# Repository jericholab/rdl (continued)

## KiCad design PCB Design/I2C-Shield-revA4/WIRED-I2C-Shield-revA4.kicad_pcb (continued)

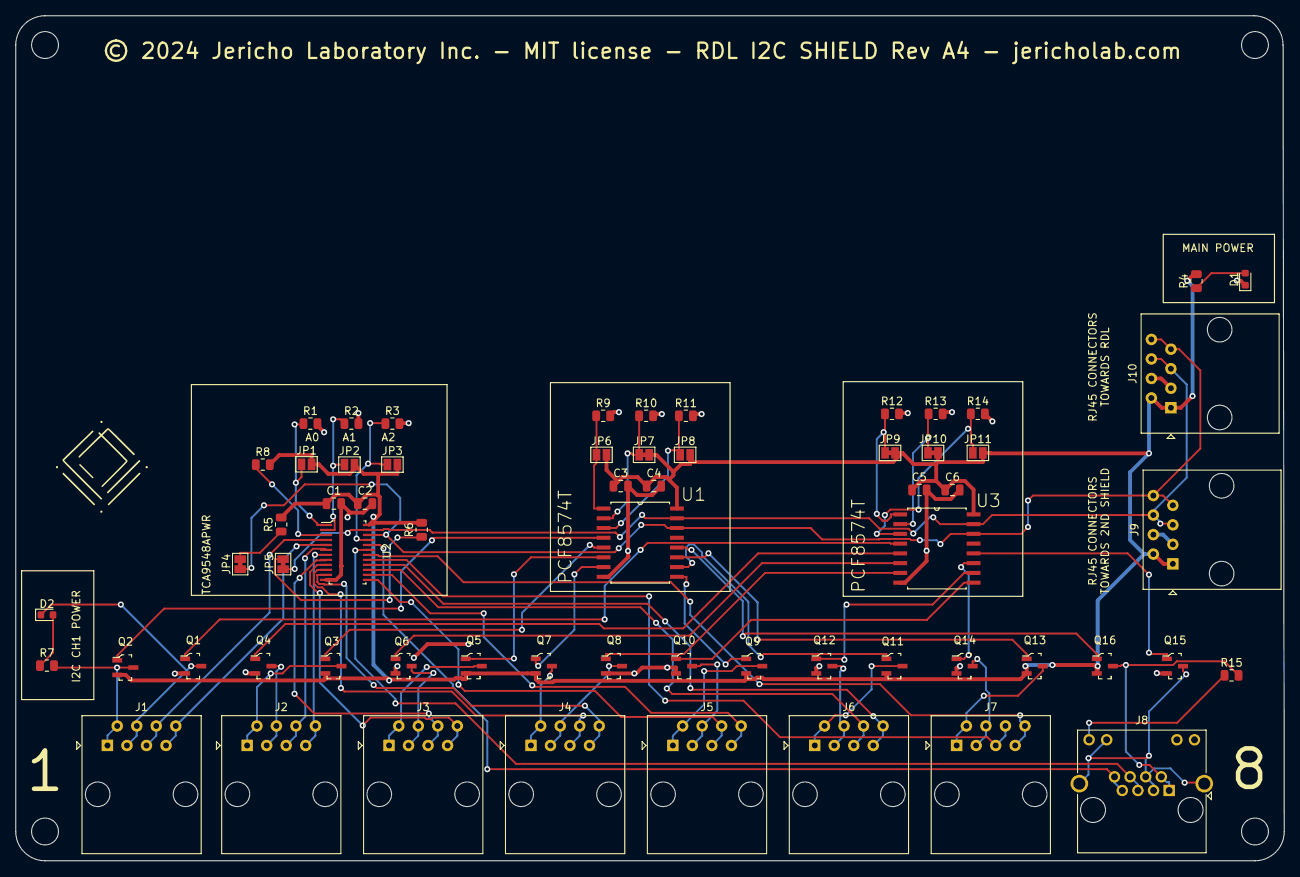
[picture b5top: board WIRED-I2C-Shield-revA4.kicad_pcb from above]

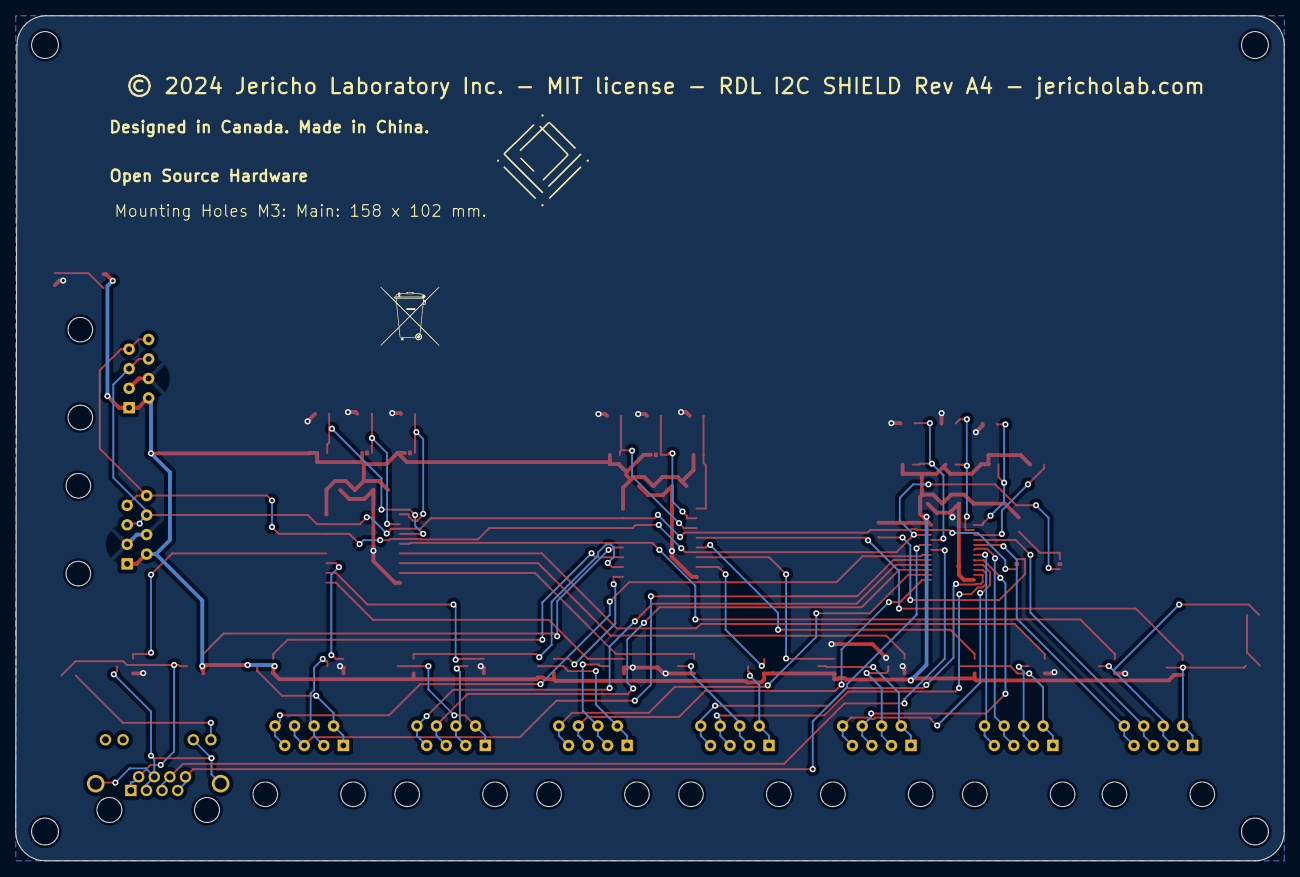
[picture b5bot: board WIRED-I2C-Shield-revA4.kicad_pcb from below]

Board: 2 copper layers, 165.1 x 110.0 mm, 70 parts (2 on the bottom side), 67 nets.

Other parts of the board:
G1, G2: LOGO; jericho-logo-kicad
G3: LOGO; Do not throw to garbage logo WEEE2
H1, H2, H3, H4: MountingHole_3.5mm

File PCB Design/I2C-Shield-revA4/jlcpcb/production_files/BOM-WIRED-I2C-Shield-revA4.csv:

Comment,Designator,Footprint,LCSC
 TCA9548APWR,U2,TSSOP-24_W4.40mm,C130026
100K,R8,R_0805_2012Metric,C149504
AO3401A,"Q11,Q13,Q16,Q2,Q3,Q5,Q7,Q9",SOT-23-3,C15127
10uF,"C1,C2,C5",C_0805_2012Metric,C15850
10K,"R15,R4,R5,R6,R7",R_0805_2012Metric,C17414
AO3406,"Q1,Q10,Q12,Q14,Q15,Q4,Q6,Q8",SOT-23-3,C20917
RED,"D1,D2",D_0603_1608Metric,C2286
PCF8574T,"U1,U3",SOIC127P1032X265-16N,C2987288
RJ45,"J1,J10,J2,J3,J4,J5,J6,J7,J9",RJ45_Amphenol_54602-x08_Horizontal,C3000197
8P8C_LED,J8,RJ45_Amphenol_RJHSE538X,C386757
20k,"R1,R10,R11,R12,R13,R14,R2,R3,R9",R_0805_2012Metric,C4328
0.1uF,"C3,C4,C6",C_0805_2012Metric,C49678

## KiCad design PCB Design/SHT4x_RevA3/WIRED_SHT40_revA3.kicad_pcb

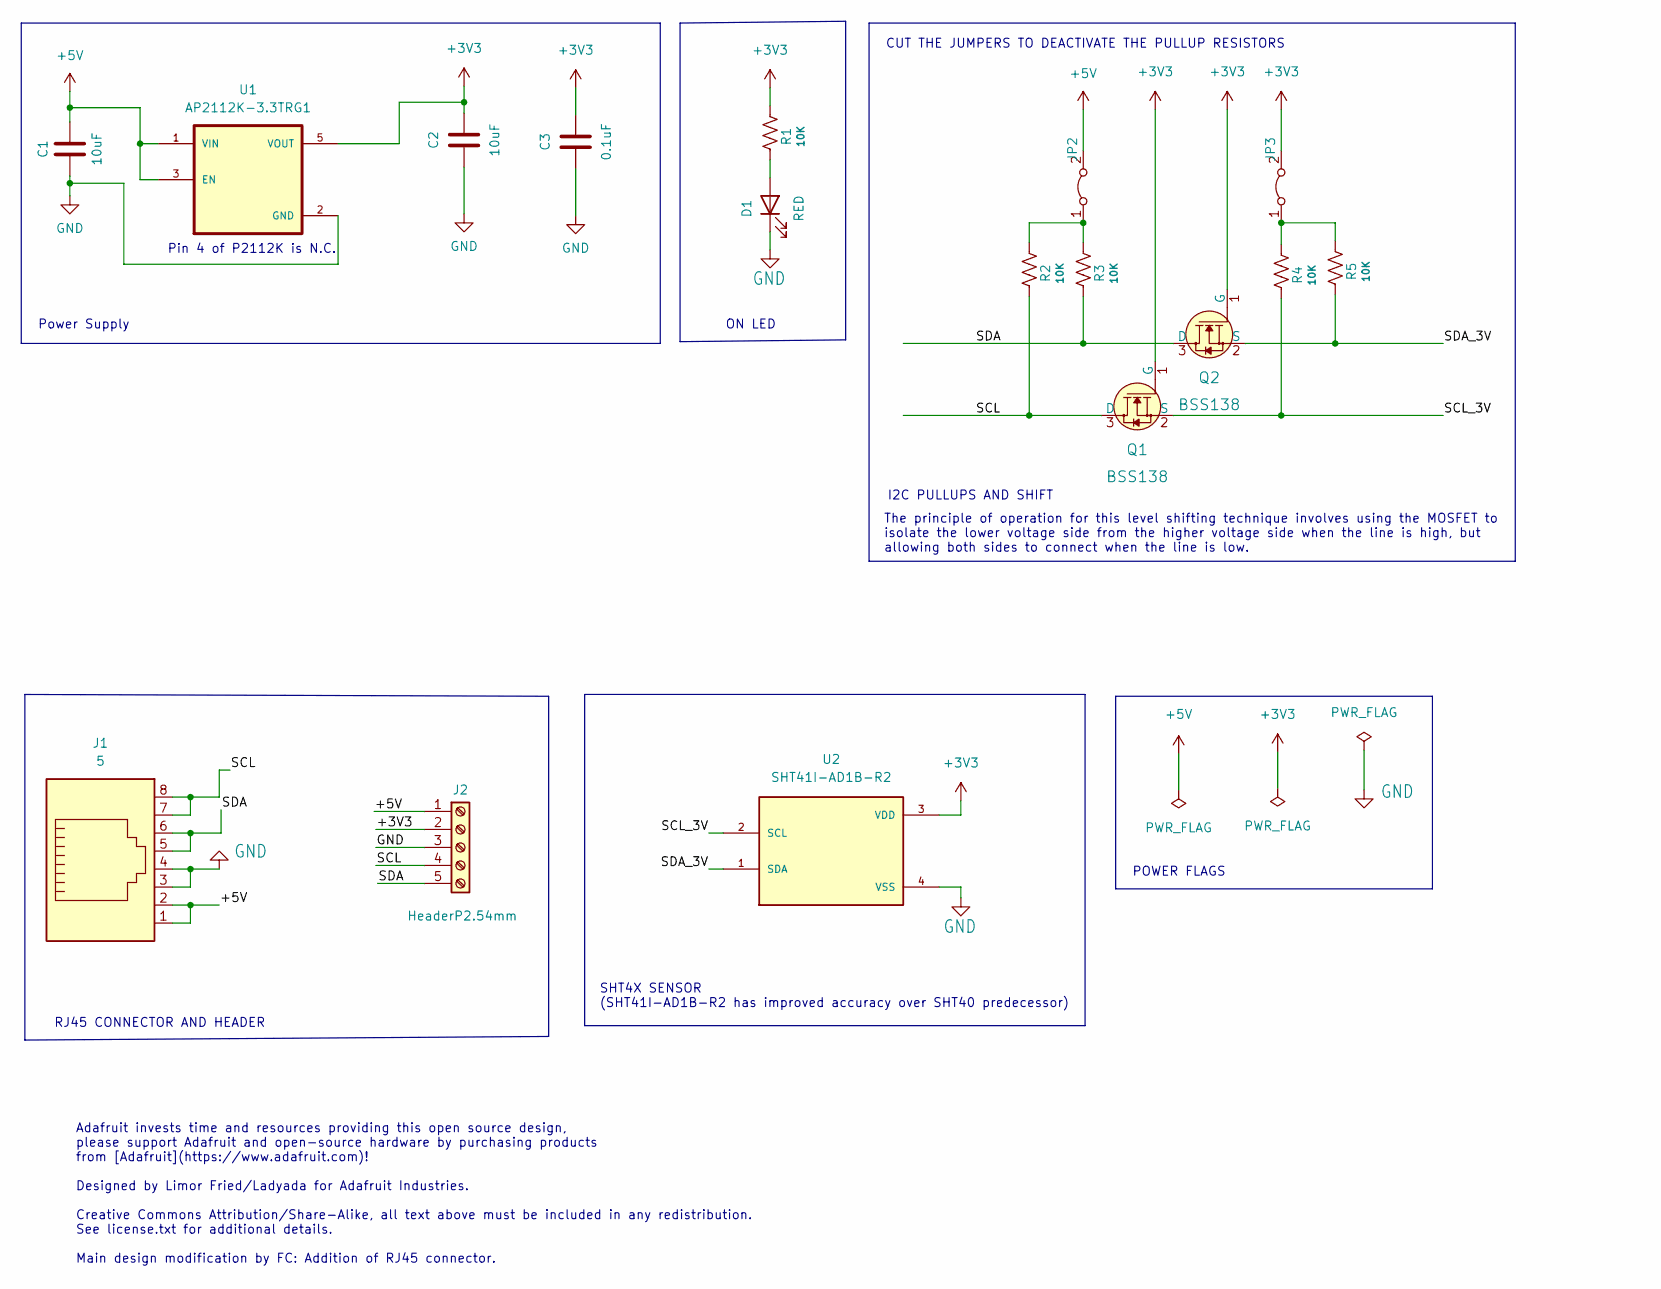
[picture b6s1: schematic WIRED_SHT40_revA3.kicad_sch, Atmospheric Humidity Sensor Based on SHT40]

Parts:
C1, C2: 10uF; C_0805_2012Metric; LCSC C440198
C3: 0.1uF; C_0805_2012Metric; LCSC C49678
D1: RED; D_0603_1608Metric; LCSC C2286
J1: 5; RJ45_Amphenol_54602-x08_Horizontal; LCSC C3000197
J2: HeaderP2.54mm; PinHeader_1x05_P2.54mm_Vertical; LCSC C706877
JP2, JP3: Jumper_2_Bridged; SolderJumper-2_P1.3mm_Bridged_Pad1.0x1.5mm
Q1, Q2: BSS138; SOT-23-3; MPN BSS138; Digi-Key_PN BSS138CT-ND
R1, R2, R3, R4, R5: 10K; R_0805_2012Metric; LCSC C17414
U1: AP2112K-3.3TRG1; SOT95P285X140-5N; PARTREV 2-2; LCSC C51118
U2: SHT41I-AD1B-R2; SHT4X; LCSC C3664410

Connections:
+3V3: C2.1, C3.1, J2.2, JP3.2 (B), Q1.1 (G), Q2.1 (G), R1.2, U1.5 (VOUT), U2.3 (VDD)
+5V: C1.1, J1.1, J1.2, J2.1, JP2.2 (B), U1.1 (VIN), U1.3 (EN)
/SCL: J1.7, J1.8, J2.4, Q1.3 (D), R2.1
/SCL_3V: Q1.2 (S), R4.1, U2.2 (SCL)
/SDA: J1.5, J1.6, J2.5, Q2.3 (D), R3.1
/SDA_3V: Q2.2 (S), R5.1, U2.1 (SDA)
GND: C1.2, C2.2, C3.2, D1.1 (K), J1.3, J1.4, J2.3, U1.2 (GND), U2.4 (VSS)
unnamed: D1.2 (A), R1.1
unnamed: JP2.1 (A), R2.2, R3.2
unnamed: JP3.1 (A), R4.2, R5.2

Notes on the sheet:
SHT4X SENSOR (SHT41I-AD1B-R2 has improved accuracy over SHT40 predecessor)
Power Supply
ON LED
Adafruit invests time and resources providing this open source design, please support Adafruit and open-source hardware by purchasing products from [Adafruit](https://www.adafruit.com)! Designed by Limor Fried/Ladyada for Adafruit Industries. Creative Commons Attribution/Share-Alike, all text above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
Pin 4 of P2112K is N.C.
POWER FLAGS
RJ45 CONNECTOR AND HEADER
The principle of operation for this level shifting technique involves using the MOSFET to isolate the lower voltage side from the higher voltage side when the line is high, but allowing both sides to connect when the line is low.
I2C PULLUPS AND SHIFT
CUT THE JUMPERS TO DEACTIVATE THE PULLUP RESISTORS

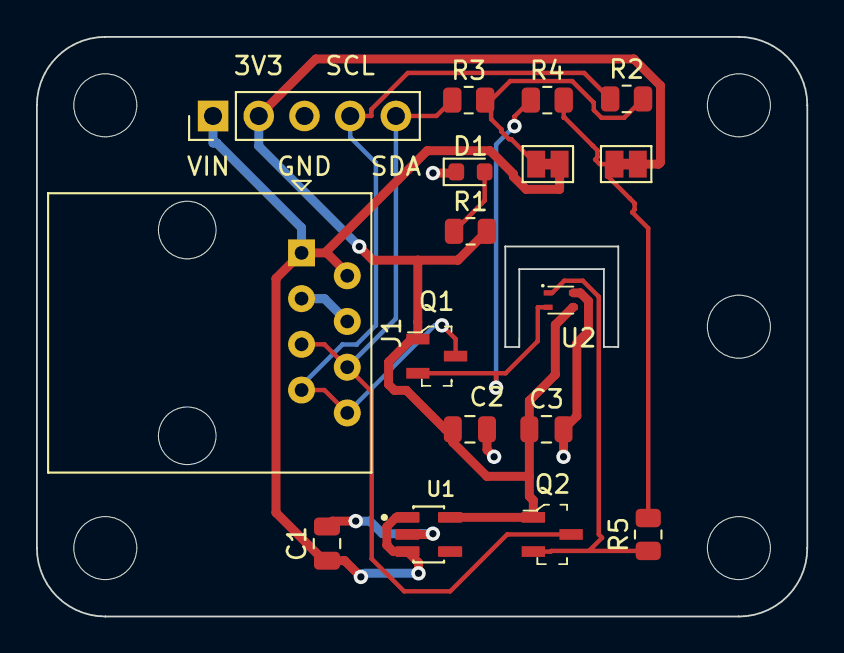
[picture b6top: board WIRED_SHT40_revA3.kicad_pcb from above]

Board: 2 copper layers, 42.8 x 32.2 mm, 23 parts (1 on the bottom side), 10 nets.

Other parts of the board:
G1: LOGO; Do not throw to garbage logo WEEE2
H1, H2, H3, H4, H5: MountingHole_3.5mm

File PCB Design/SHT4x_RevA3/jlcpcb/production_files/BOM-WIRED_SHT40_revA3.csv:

Comment,Designator,Footprint,LCSC
10K,"R1,R2,R3,R4,R5",R_0805_2012Metric,C17414
RED,D1,D_0603_1608Metric,C2286
5,J1,RJ45_Amphenol_54602-x08_Horizontal,C3000197
SHT41I-AD1B-R2,U2,SHT4X,C3664410
10uF,"C1,C2",C_0805_2012Metric,C440198
0.1uF,C3,C_0805_2012Metric,C49678
AP2112K-3.3TRG1,U1,SOT95P285X140-5N,C51118
HeaderP2.54mm,J2,PinHeader_1x05_P2.54mm_Vertical,C706877
BSS138,"Q1,Q2",SOT-23-3,C7420339

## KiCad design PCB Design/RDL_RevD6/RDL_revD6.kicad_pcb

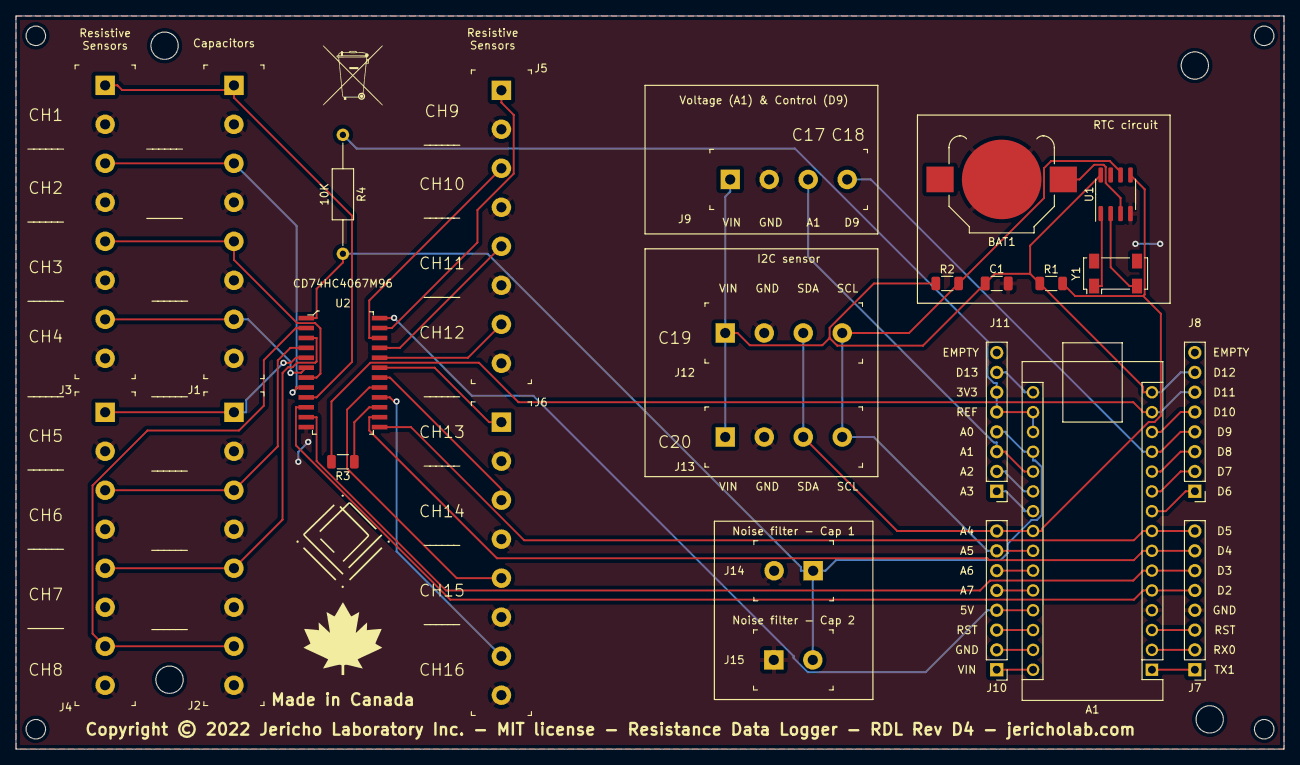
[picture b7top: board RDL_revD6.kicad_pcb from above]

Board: 2 copper layers, 162.6 x 94.0 mm, 35 parts (0 on the bottom side), 49 nets.

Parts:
A1: Arduino_Nano_v3.x; Arduino_Nano
BAT1: 3V; BatteryHolder_Keystone_3000_1x12mm
C1: 1 uF; C_1206_3216Metric
G1: LOGO; Do not throw to garbage logo WEEE2
G2: LOGO; made-in-canada
H1, H2, H3, H4: MountingHole_2.5mm
H5, H6, H7, H8: MountingHole_3.5mm
J1, J2, J3, J5: Screw_Terminal_01x08; Term_Block_1x8_P5mm
J4, J6: Term_Block_1x8_P5mm
J7, J8, J10, J11: Screw_Terminal_01x15; PinHeader_1x08_P2.54mm_Vertical
J9, J13: Term_Block_1x4_P5mm
J12: Screw_Terminal_01x04; Term_Block_1x4_P5mm
J14: Term_Block_1x2_P5mm
J15: OSTTC020162; Term_Block_1x2_P5mm
R1, R2: 10k; R_1206_3216Metric
R3: 10K; R_1206_3216Metric
R4: 10K; R_Axial_DIN0207_L6.3mm_D2.5mm_P15.24mm_Horizontal
U1: DS1307ZN+; SOIC-8_3.9x4.9mm_P1.27mm
U2: CD74HC4067M96; SOIC-24_W7.50mm
Y1: Crystal; Crystal_SMD_Abracon_ABS25-4Pin_8.0x3.8mm

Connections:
+BATT: BAT1.1, U1.3 (VBAT)
/CH1: J1.1, J3.1, U2.9 (I0)
/CH2: J1.3, J3.3, U2.8 (I1)
/CH3: J1.5, J3.5, U2.7 (I2)
/CH4: J1.7, J3.7, U2.6 (I3)
/CH5: J2.1, J4.1, U2.5 (I4)
/CH6: J2.3, J4.3, U2.4 (I5)
/CH7: J2.5, J4.5, U2.3 (I6)
/CH8: J2.7, J4.7, U2.2 (I7)
/CH9: J5.1, U2.23 (I8)
/CH10: J5.3, U2.22 (I9)
/CH11: J5.5, U2.21 (I10)
/CH12: J5.7, U2.20 (I11)
/CH13: J6.1, U2.19 (I12)
/CH14: J6.3, U2.18 (I13)
/CH15: J6.5, U2.17 (I14)
/CH16: J6.7, U2.16 (I15)
/GND: A1.4 (GND), BAT1.2, C1.2, J1.2, J1.4, J1.6, J1.8, J2.2, J2.4, J2.6, J2.8, J3.2, J3.4, J3.6, J3.8, J4.2, J4.4, J4.6, J4.8, J5.2, J5.4, J5.6, J5.8, J6.2, J6.4, J6.6, J6.8, J7.4, J9.2, J12.2, J13.2, J14.2, J15.1, U1.4 (GND), U2.12 (GND)
/OSCI: U1.1 (X1), Y1.1
/OSCO: U1.2 (X2), Y1.2
/SCL: A1.24 (A5), J10.7, J12.4, J13.4, R2.2, U1.6 (SCL)
/SDA: A1.23 (A4), J10.8, J12.3, J13.3, R1.2, U1.5 (SDA)
/VCC15: A1.15 (D12), C1.1, J8.7, J9.1, J12.1, J13.1, R1.1, R2.1, U1.8 (VCC)
/pin1: A1.1 (D1/TX), J7.1
/pin2: A1.2 (D0/RX), J7.2
/pin3: A1.3 (~RESET), J7.3
/pin5: A1.5 (D2), J7.5, U2.10 (S0)
/pin6: A1.6 (D3), J7.6, U2.11 (S1)
/pin7: A1.7 (D4), J7.7, U2.14 (S2)
/pin8: A1.8 (D5), J7.8, U2.13 (S3)
/pin9: A1.9 (D6), J8.1
/pin10: A1.10 (D7), J8.2
/pin11: A1.11 (D8), J8.3
/pin12: A1.12 (D9), J8.4, J9.4
/pin13: A1.13 (D10), J8.5
/pin14: A1.14 (D11), J8.6, R3.2
/pin16: A1.16 (D13), J11.7
/pin17: A1.17 (3V3), A1.18 (AREF), J11.5, J11.6, R4.1
/pin19: A1.19 (A0), J11.4, J14.1, J15.2, R4.2, U2.1 (COM)
/pin20: A1.20 (A1), J9.3, J11.3
/pin21: A1.21 (A2), J11.2
/pin22: A1.22 (A3), J11.1
/pin25: A1.25 (A6), J10.6
/pin26: A1.26 (A7), J10.5
/pin27: A1.27 (+5V), J10.4, U2.24 (VCC)
/pin28: A1.28 (~RESET), J10.3
/pin29: A1.29 (GND), J10.2
/pin30: A1.30 (VIN), J10.1
unnamed: R3.1, U2.15 (E)

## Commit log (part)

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2024-03-04 Update I2C bus release strategy for SHT40
    SHT40: Adding tca_init() before cutting power to the MUX channel avoids the I2C bus jam even for 30m CAT cable. This is a great improvement. Delays have also been added to improve odds (effect not an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
2024-03-04 Update pH integration
    After verification, pH works in the main RJ45 but does not work with MUX. Most likely because both pH and MUX use the Wire.beginTransmission() statement. We will fix this in the near future.
2024-03-07 Small test
2024-03-15 Create read me
2024-03-16 Add new version of freerouting
2024-03-16 Move files into folder
2024-03-16 Copy the daemons from repo2 to repo1
2024-03-20 Transfer Python Scripts to revE3-dev branch
2024-03-20 Change of folder
    Changed the folder
2024-03-28 I2C channels indexed to 1 instead of 0
    It seems that the pH has started working with MUX, for unknown reasons.
2024-03-29 Fix the architecture syncing
2024-03-29 Add SDCard name to config.json
2024-04-02 Print config file
2024-04-03 add restart delay to avoid excessive restart error
    daemon
2024-04-05 Add auto-restart delay to all scripts
2024-04-15 Revert "Update Design Overview - Hall Effect Current Sensor.md"
    This reverts commit 6b13d49b5094f1fc889f931371df9bcf953b1d76.
2024-04-15 Revert "Update Design Overview - IP Camera System.md"
    This reverts commit 030f383963c4bf70e68250a6ecf72a2af7411dc2.
2024-04-17 Small change for demonstration
2024-04-17 Revert "Small change for demonstration"
    This reverts commit 47ea68b3fd4733a533b77c60092434afc880c4d3.
2024-04-20 Add 3D model ir-cam-adapter to documentation
2024-04-21 Add 3D model of grid-for-SBC-fan to documentation
2024-04-21 Add 3D Model - Radiation Shield and Hub Bracket
2024-04-21 Add NAU7802_revB1 PCB design to documentation
2024-04-21 Cleanup the PCB Design folder
2024-04-21 Add pH-EZO-Carrier-revA1 PCB design to documentation
2024-04-21 Add RDL_RevE4 PCB Design to Documentation
2024-04-21 Create oldGen folder and add missing pdf SHT4x
2024-04-21 Delete Ice-bath-device-revB4.zip
    Remove duplicate. File can now be found in/3DCAD.
2024-04-21 Normalize the file naming by removing some spaces
2024-04-21 Retrieving the correct version of the ice bath procedure
2024-04-22 Finalize the calibration procedure Warm Bath 3.2
2024-04-23 Create and update all Documentation for the Python Scripts (4)
2024-04-23 Major update on strain sensor design overview
2024-04-23 Major update on Atm Humidity Sensor
2024-04-25 Major update on Design Overview for Infrared Camera (WIP)
2024-04-26 Add csv-to-jpeg functionality
2024-04-26 Rename Design Overview file
2024-04-29 Major updates to Thermal Camera and Main Hub Documentation
2024-04-29 Added auto daily foldering
2024-04-30 Add daily folder to thermal cam script
2024-04-30 Harmonize csv-to-img with foldering and transfer to infrared.py
2024-04-30 Minor corrections
2024-04-30 Transfer Hall Effect into Strain Sensor Doc (WIP)
2024-05-01 More updates on the NAU7802 doc
2024-05-02 Fix thermal camera buffer problem
    Other minor modifications
2024-05-03 Add PCB integration section to NAU7802 doc
    Also added a schematic
2024-05-03 Minor update
2024-05-18 Temporary image for readme
2024-06-11 Rename EDITED Picture-NAU7802-revB1.jpg to EDITED-Picture-NAU7802-revB1.jpg
2024-06-11 Create test2
2024-06-12 Rename EDITED Picture-RDL-revE4-croppedCopy.jpg to Picture-RDL-revE4.jpg
2024-06-12 Rename EDITED Picture-RDL-revE4.jpg to Picture-RDL-revE4.jpg
2024-06-19 Final updates on NAU7802 Design Overview
2024-06-21 Rename RDL Overview to E4
2024-06-21 Major update on RDL design overview (from E2 to E4)
2024-06-23 Create first version of thermal camera carrier board revA1
2024-06-26 Update two little codes to change EZO-pH mode
2024-06-27 Minor corrections on currentNAU7802 function
2024-06-28 Add force to strainFunction
2024-06-29 Minor modifications
2024-06-29 Some improvements on NAU7802 MUXing
2024-06-29 Update strainFunc.ino
    This Update gave very first successful load cell measurement with a multiplexed TAL220
2024-07-11 Adapt scripts and daemons to from Orange to RPI
    New content successfully tested on Raspberry
    Include the seekcamera-python wrapper.
    Remove old file.
2024-07-11 Config.txt for headless and monitor modes
2024-07-31 Partial development
2024-08-01 Update allows basic mux for strain NAU7802
    Addition of enable(true) and enable(false) statements to put the nau7802 sensor into power down mode, which allows to revive the sensor at each loop without a new begin() statement , which caused mem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
2024-08-01 Adjust Headers for multiple Teros
    Although not part of NAU7802 work, I just added this little correction.
2024-08-03 Fix basic reading Current-NAU7802 (still Sparkfun)
2024-08-03 Modifications to bring MUX feature to Current-NAU7802
2024-08-03 Fully functional MUX on current-nau7802
    Accuracy seems reasonable but could maybe be improved with some register options.
2024-08-05 Successful MUX of strain-nau7802
    Tolerates all conditions and cohabitation with strain sensor. Only minor default is that the offset has changed slightly to 0.48V for unknown reasons. Multimeter reads 0.52V. Some cleanup in the code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
2024-08-05 Update offset value
2024-08-14 Removed all wire.setClock() statements
    Since the TWI library now operates at low speed by default (489Hz), there is no need to override the I2C clock speed anymore.
2024-08-15 Create backup found
2024-08-16 Add modified twi library file with instructions
2024-09-02 Add RustDesk reinstall script
    Reinstallation is necessary on RPI to generate a different RustDesk ID than the clone image.
2024-09-02 Use 15-min default interval on Reolink script
2024-09-18 Remove empty folders locally before upload to Cloud
    This will avoid the accumulation of a large number of empty folders on the Dropbox cloud in the case where one of the cameras is not connected for example.
2024-10-04 Add long interval capacity to thermal camera
    Dummy output every minute with occasional real output (jpeg & csv) when timer out. Timer value controled by config.json.
2024-10-08 Adding internet access monitoring (script & daemon)
    Also numbering of folders (1_inprogress, 2_tosync, 3_transit, 4_synced)
2024-10-12 Create unique name for readMode of voltage readings
2024-10-22 Add support for second reolink camera
    Requires second camera and a switch
2024-10-23 Add script to verify version of twi.c
    Original twi.c or modified (slow) twi.c file detected.
2024-11-03 Add detection for RDL jam
    If jam of 15 minutes detected, then break from function, and hence script stops. Service will restart script. Also, only try to read serial if serial has data waiting. Also clean file from old commen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
2024-11-04 Add timestamp to jam threshold error message
2024-11-05 Add detection of daylight saving time
    The Arduino RTC timestamp should always display regular time, even if you live in a region where Daylight Saving Time applies. This is because the RTC DS3231 cannot apply DST by itself or via the RTC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
    Added optional removal (if you are not in a DST area) and also adjusted header column for time.
2024-11-06 Improve Summer Time Management
    Proper detection of Summer Time at Compile time. Function applies Regular Time always. New separate function for setting Time (setTime), that can be called with new command SETTIME.
2024-11-19 Create 5000Hz version of twi.c (untested)
2025-01-17 Add logging of RustDesk ID to script
    In case, RustDesk decides to change the ID, the remote user can reconnect.
2025-01-17 Add disk usage monitoring and control
    Add disk use (%) display in log file (internet_access.py)
    Add automatic deactivation of all daemons when disk usage above threshold (default 95%)
2025-01-23 Reduced delays in calls to current and strain functions
    These high delays reduced the acquisition frequency with no obvious benefits. Note: This code was used successfully to measure 200 consecutive current sensor values with MUX Shield (Channel 5) and 75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
2025-02-03 Add getI2Cfreq() function
    Display at startup the clock speed at which the I2C bus is running. This will avoid user running at wrong clock speed by inadvertence
2025-02-06 Minor correction for line and spacing
2025-02-18 Correct comma mistakes
2025-02-19 Add functionality automatic emails
    Schedules emails (SendGrid) contain sample of latest local data found.
2025-02-24 Add ability to handle missing type of files
    If the unit has no camera or RDL, the missing file should not prevent the automatic email from being sent.
2025-03-06 Remove network condition for specific daemons
    Some daemons do not require an internet connection to do their job.
2025-03-06 Revert "Remove network condition for specific daemons"
    This reverts commit 3bdc01257863689e8a5d9bdbcc6d344eff66d9a6.
2025-03-08 Add flag to force immediate sensor read
    After setup() and after change of measurement interval via serial window command, the flag1 boolean is used to force the reading of sensors, independently of time elapse.
2025-03-09 Minor adjustments pH function when multiplexed
    pH probe function started working today for unknown reason. Adjustment was made to clear ph_data values in between channel readings.
2025-03-18 New branch with irradiation and wind sensor
2025-03-21 Comment temporary test
2025-03-28 Minor modifications
    New line before printing "No data received in 2 minutes"
    Modifications to optimize memory usage.
2025-04-03 Added support for multiple strain gauge cell
    Transfer strain calibration values out of the function.
    Arduino code now reads strain calibration values from header file (.h).
    Created Excel file containing calibration procedure and calib values.
    New Python script (runMe.py) that creates calibration header file from Excel file.
    Add moment value display and adjust printed header.
2025-04-09 Correct moment formula
    Moment = force times distance, not divided.
2025-04-11 Put calculatePhi() in separate file
    Putting function in separate file to make it more compatible with PlatformIO conversion by script. Also put zero offset value outside of currentNAU7802 function to prepare terrain for channel-specifi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
2025-04-14 Add 0.00 column when absent strain sensor
2025-04-15 Add 2min delay to pH routine for probe warm up
    Without 2min warm up, the probe value is not converged. This is critical for multiplexed cases, where the probe is not continuously under tension. Ideally, it would need 10min to reach 99% of the asy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
2025-05-08 Add temperature compensation to current sensor
    Dummy values replaced with real values based on exp 2025-05-03-Freezer. Large improvement on reliability of current sensor across large temperature span (-10 to +40C). Highly linear relationship.
    Also, some old comments removed and other minor corrections.
2025-05-08 Remove hard coded T_channel for current func
    Explicit the temperature probe channel number to be used for all current sensors.
2025-05-19 New script to merge data files recursively
    Completely new script generated by GPT to merge data txt files even when they are scattered across several subfolders
2025-06-22 Clear signal when algo rejects NAU sample
    If there is no communication, ADC reads -1.
    If there is at least one sample rejected by outlier detection algo, ADC reads -222.
2025-08-09 Minor updates and cleanup
    Deleted some old functions and comments as I updated the documentation (SAD)
2025-08-11 Add coefficient library for current sensor calibration
    current_coefficients.h
    Other minor corrections and cleaning
2025-08-12 Fixed the NaN display problem for thermistors
    Solved for both ADS (10-bit, 16-bit)
    Also moved the readMode variable to user parameters section.
2025-08-24 Improve log file behavior
    Syncing log file in /logging-folder instead of root.
    Max size of 10MB for log file (erase).
2025-08-24 Create jericho-ezo-pH-calibration.ino
    Add a new code that allows auto-read pH values (optional) as well as serial commands (read, calibrate, etc).
2025-08-26 Doubling R_MUX value to 140ohm
    Doubling the value to account for the multiplexer electrical resistance (70 ohm) which is added twice on the voltage divider circuit.
2025-09-25 Update filename for chart
2026-02-22 Minor correction
2026-05-22 cleaned project
2026-05-25 added avr_nano_every way of calculating frequency
